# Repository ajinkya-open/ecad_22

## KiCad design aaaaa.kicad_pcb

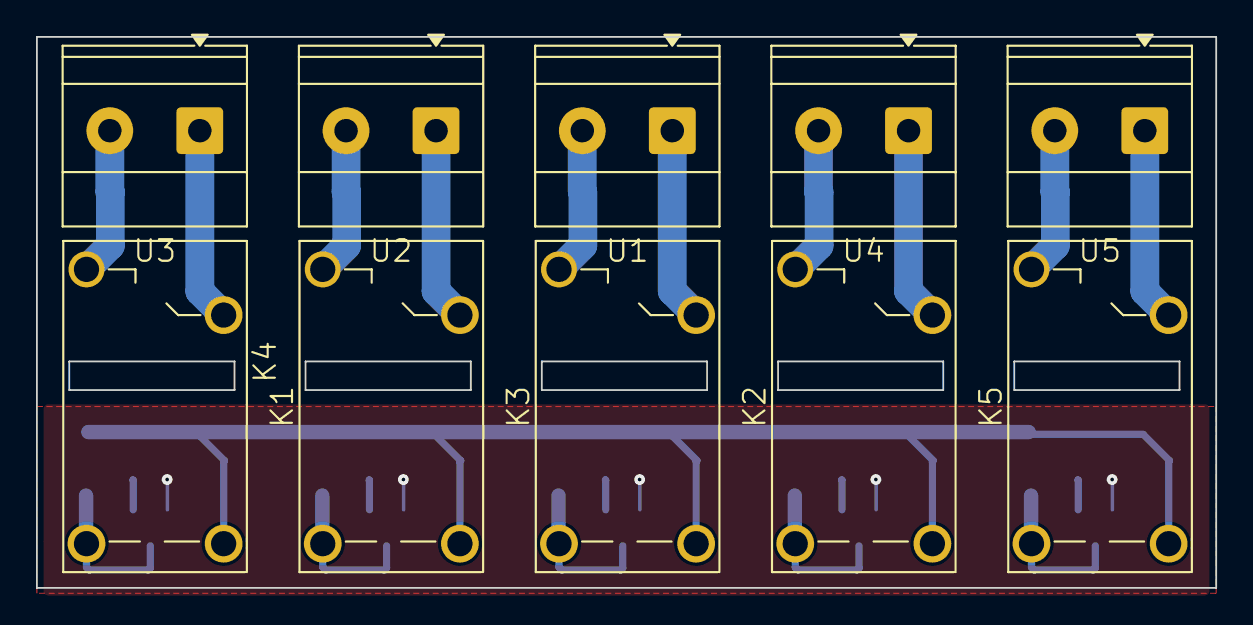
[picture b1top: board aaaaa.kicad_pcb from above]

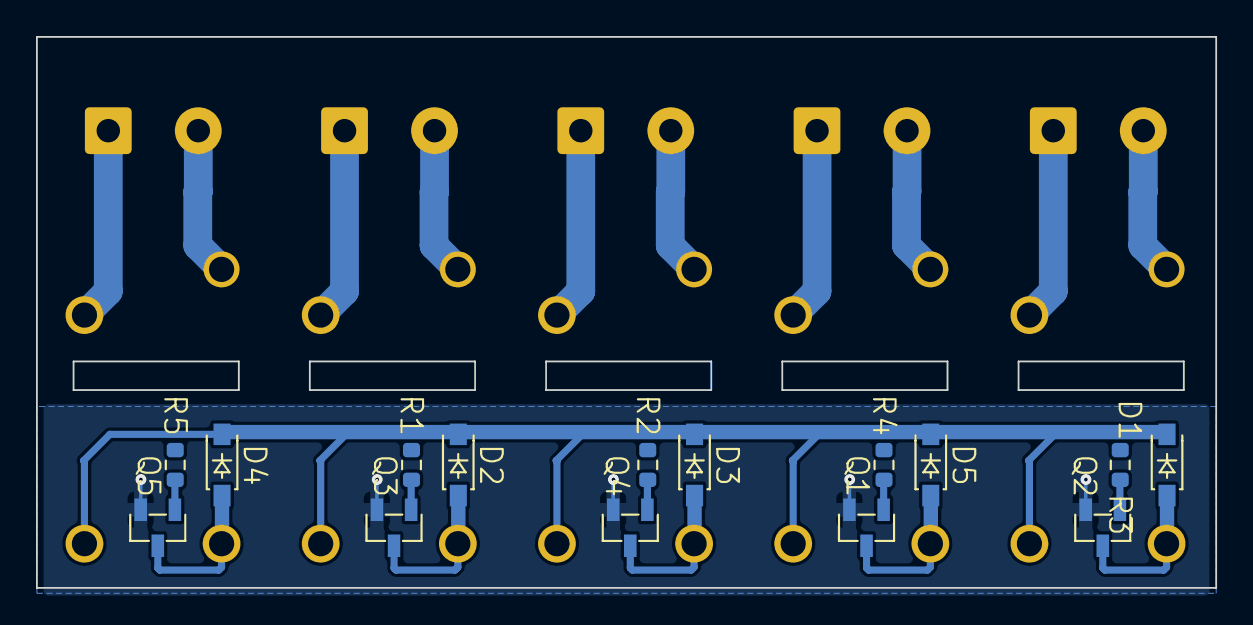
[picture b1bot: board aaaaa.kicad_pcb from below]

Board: 2 copper layers, 65.5 x 30.6 mm, 25 parts (15 on the bottom side), 22 nets.

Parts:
D1, D2, D3, D4, D5: 1N4148W-7-F; SOD-123_L2.7-W1.6-LS3.7-RD-1
K1, K2, K3, K4, K5: HF32; RELAY-TH_HF32FV-G-5-HSTF-590
Q1, Q2, Q3, Q4, Q5: BC817-25_C20069154; SOT-23-3_L2.9-W1.3-P0.95-LS2.4-BR
R1, R2, R3, R4, R5: 2K2; R_0603_1608Metric
U1, U2, U3, U4, U5: MKDSN 2,5/ 2-5,08; TerminalBlock_Phoenix_MKDS-1,5-2_1x02_P5.00mm_Horizontal

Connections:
GND: Q1.2 (E), Q2.2 (E), Q3.2 (E), Q4.2 (E), Q5.2 (E)
unnamed: D1.2 (A), K4.2, Q2.3 (C)
unnamed: D2.2 (A), K2.2, Q3.3 (C)
unnamed: D3.2 (A), K3.2, Q4.3 (C)
unnamed: D4.2 (A), K5.2, Q5.3 (C)
unnamed: D5.2 (A), K1.2, Q1.3 (C)
unnamed: K1.3, U2.1
unnamed: K1.4, U2.2
unnamed: K2.3, U4.1
unnamed: K2.4, U4.2
unnamed: K3.3, U1.1
unnamed: K3.4, U1.2
unnamed: K4.3, U3.1
unnamed: K4.4, U3.2
unnamed: K5.3, U5.1
unnamed: K5.4, U5.2
unnamed: Q1.1 (B), R4.2
unnamed: Q2.1 (B), R3.2
unnamed: Q3.1 (B), R1.2
unnamed: Q4.1 (B), R2.2
unnamed: Q5.1 (B), R5.2
VCC_5V: D1.1 (C), D2.1 (C), D3.1 (C), D4.1 (C), D5.1 (C), K1.1, K2.1, K3.1, K4.1, K5.1

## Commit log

2026-03-24 init
2026-03-24 Variant Swap: layout2 -> master @ 16:24:34
2026-03-24 sdcs
